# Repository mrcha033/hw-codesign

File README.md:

# hw-codesign

**Give an AI agent a hardware brief. Get KiCad, firmware, a 3D assembly, and an explicit fabrication-blocker report.**

Agentic hardware co-design from brief to KiCad, firmware, 3D review, and explicit
fabrication blockers. For 13 supported board families, `hw-codesign` turns a
prompt into a reviewable candidate while keeping missing sourcing, toolchain,
manufacturing, and physical evidence visible instead of silently treating it as
success.

<p align="center">
  
</p>

<p align="center">
  <strong><a href="https://mrcha033.github.io/hw-codesign/#assembly-title">Explore the interactive 3D review</a></strong><br>
  Rotate and zoom the generated RP2040 USB candidate, then inspect its evidence and unresolved blockers.
</p>

[Explore the interactive 3D review](https://mrcha033.github.io/hw-codesign/#assembly-title) ·
[Install from PyPI](https://pypi.org/project/hw-codesign/) ·
[Watch the 20-second demo](docs/demo/README.md) ·
[Read the validation contract](docs/validation-contract.md)

The render is a candidate-level CAD preview, not a photo of fabricated or
qualified hardware.

## Quickstart

Python 3.11 or newer is required. This public install path was smoke-tested in a
clean Python 3.11 environment against version 0.1.4.

```bash
python3.11 -m pip install "hw-codesign[mcp]==0.1.4"
mkdir my-hardware-workspace && cd my-hardware-workspace
hw --root . create-project my_usb_board --template rp2040_usb_device
hw --root . validate-spec my_usb_board
```

That creates and validates a typed RP2040 project. Continue to
[generate the full demo candidate](#generate-the-demo-candidate), or run
`hw --help` to inspect the CLI.

<details>
<summary><strong>What the public demo proves—and what remains blocked</strong></summary>

<!-- golden-demo-evidence:start -->
The demo is a dated full-toolchain repository run against the RP2040 USB-device
family. It produced a candidate, not a fabrication-qualified board: 44 of 48
recorded gates passed, 1 failed, and 3 were blocked. Freerouting reports zero
raw unrouted connections and KiCad reports zero post-fill unconnected items;
native ERC and DRC each report zero violations. The native Zephyr build is
blocked because the selected ARM toolchain lacks newlib runtime files.

The remaining evidence is material: sourcing fails, current supplier
availability is blocked, the native Zephyr build is blocked on ARM newlib, and
physical qualification is blocked. The
board has not been fabricated, and the U2.57 via-in-pad fill/cap/tent process is
unqualified. Bundle `7d6731501a24716965593f7fcdc168a3d739d1b0a1b7a57f7a0b29fee51c1b84` records those boundaries.
<!-- golden-demo-evidence:end -->

</details>

## The 20-second product loop

| Brief | Candidate | Blocker report |
|---|---|---|
| Natural-language constraints are lowered into typed project fields with provenance. | The run emits electronics source, KiCad artifacts, firmware, BOM, review bundle, and hashes. | Every gate is `pass`, `fail`, or `blocked`; physical evidence gaps stay release-blocking. |

`hw-codesign` is available as a CLI (`hw`), an MCP server (`hw-mcp`), and a
repository-owned agent plugin. Its design surface is template- and
contract-driven. It is not an arbitrary-prompt PCB oracle.

## Install

Python 3.11 or newer is required.

```bash
python3.11 -m pip install "hw-codesign[mcp]==0.1.4"
hw --help
```

The [v0.1.4 release](https://github.com/mrcha033/hw-codesign/releases/tag/v0.1.4)
also publishes a wheel, source distribution, standalone archives for Linux,
macOS, and Windows, a self-contained review, and checksums. The public container
is `ghcr.io/mrcha033/hw-codesign:0.1.4`.

### Development install

```bash
git clone https://github.com/mrcha033/hw-codesign.git
cd hw-codesign
python3.11 -m venv .venv
.venv/bin/pip install '.[mcp]'
export PATH="$PWD/.venv/bin:$PATH"
hw --help
```

The self-contained review is live at
https://mrcha033.github.io/hw-codesign/ and can be inspected without a receiver
or cloud account.

## Generate the demo candidate

Create the same candidate class used in the demo:

```bash
mkdir my-hardware-workspace
cd my-hardware-workspace

hw --root . create-project my_usb_board --template rp2040_usb_device
hw --root . update-requirements my_usb_board \
  "Design a 2-layer RP2040 USB HID and CDC board powered from USB-C. Use Zephyr."
hw --root . design-candidate my_usb_board --brief \
  "Design a 2-layer RP2040 USB HID and CDC board powered from USB-C. Use Zephyr."
hw --root . export-standalone-review my_usb_board
```

The generated HTML review is self-contained. No receiver or cloud account is
required to inspect it.

### MCP clients

Claude Desktop configuration:

```json
{
  "mcpServers": {
    "hw-codesign": {
      "command": "/absolute/path/to/hw-codesign/.venv/bin/hw-mcp",
      "args": [],
      "env": {
        "HW_PLATFORM_ROOT": "/absolute/path/to/a/writable/hardware-workspace"
      }
    }
  }
}
```

Claude Code:

```bash
claude mcp add hw-codesign \
  -e HW_PLATFORM_ROOT="$PWD" \
  -- /absolute/path/to/hw-codesign/.venv/bin/hw-mcp
```

For Codex or Claude plugin use, clone this repository and install the
`hw-codesign` marketplace entry:

```bash
codex plugin marketplace add /absolute/path/to/hw-codesign
codex plugin add hw-codesign@hw-codesign
```

## What the statuses mean

| Status | Meaning |
|---|---|
| `pass` | The named gate ran and its declared checks passed. |
| `fail` | The gate ran and found a concrete defect or unmet contract. |
| `blocked` | Evidence or a required tool/input is missing. This is never treated as pass. |
| `candidate` | Reviewable generated artifacts exist, but release promotion is not authorized. |
| `released` | The configured release gate passed and the release bundle was exported. This does not imply physical qualification unless physical evidence is present and approved. |

Every public tool response carries `release_eligible`, `candidate_only`, and
`release_blocking_failures`. Only the release-gate and release-export paths can
set `release_eligible: true`.

## Supported board families

All 13 shipped templates conform to the current typed spec schema. Their design
and physical maturity are not identical; inspect each candidate's gate report.

| Group | Templates |
|---|---|
| USB devices | `rp2040_usb_device`, `usb_hid_controller`, `avr_32u4_hid`, `nrf52840_dongle` |
| Sensors and gateways | `ble_sensor_node`, `sensor_data_logger`, `lora_sensor_node`, `esp32_wifi_gateway`, `samd21_sensor_hub`, `stm32g0_power_monitor` |
| Robotics and power | `robotics_controller_full`, `mini_servo_robot`, `bldc_esc` |

Use `hw diagnose-environment` to inspect the installed native backends, or see
[Adapting the design system](docs/adapting-a-spec.md) before adding a materially
different topology.

## Agent workflow

The MCP names use the same lifecycle as the CLI:

```text
hw_get_capabilities
  → hw_create_project
  → hw_update_requirements
  → hw_design_candidate
  → hw_check_cross_domain_consistency
  → hw_generate_physical_qualification_plan
  → hw_record_physical_evidence
  → hw_check_release_gate
  → hw_export_release_bundle
```

Agents can also author circuit blocks, placement constraints, and firmware
modules, explore alternatives, compare candidates, and run adversarial grounding
benchmarks. See the [MCP tool reference](docs/mcp-tools.md) for the complete
contract.

## Build with us

- [Reproduce the PyPI quickstart on a clean platform](https://github.com/mrcha033/hw-codesign/issues/11) — the current newcomer task.
- [Share a generated candidate](https://github.com/mrcha033/hw-codesign/discussions/categories/show-and-tell) — include the prompt, template, environment, and blocker report.
- [Help close sourcing or physical-evidence gaps](https://github.com/mrcha033/hw-codesign/issues?q=is%3Aissue+is%3Aopen+label%3A%22help+wanted%22) — software-clean is not the end of the hardware lifecycle.

If a new board family or backend is your goal, start with
[Adapting the design system](docs/adapting-a-spec.md) and preserve the
`pass`/`fail`/`blocked` claim boundary in every new tool path.

## Repository map

| Path | Purpose |
|---|---|
| `src/hw_codesign/` | CLI, MCP service, generators, validators, and review UI |
| `src/hw_codesign/templates/` | Supported family specifications |
| `parts/` | Curated components, role sets, supplier records, and datasheet evidence |
| `projects/golden_rp2040_usb_hid/` | Date-stamped golden candidate and current evidence gaps |
| `docs/demo/` | 20-second demo and self-contained read-only review |
| `schemas/` | Typed project and result contracts |
| `tests/` | Cross-platform regression and evidence-boundary tests |

## Development

```bash
python3.11 -m venv .venv
.venv/bin/pip install '.[dev,mcp]'
npm ci --ignore-scripts
pytest -q
ruff check .
```

Native gates require their corresponding tools. Diagnose the current machine
before interpreting a blocked result:

```bash
hw diagnose-environment --target fabrication_release --backend kicad
hw check my_usb_board
```

See [CONTRIBUTING.md](CONTRIBUTING.md) for contribution scope, tests, and claim
boundaries. Security reports should follow [SECURITY.md](SECURITY.md).

## Known limits

- Generated artifacts remain candidates until every configured release gate
  passes. A Gerber ZIP is not proof that a board is safe or manufacturable.
- Digital checks cannot certify thermal performance, EMI/EMC, vibration,
  ingress, abuse safety, connector life, assembly quality, or electrical
  bring-up. Those require traceable physical evidence.
- The RP2040 golden candidate has not yet been fabricated. Its current blocker
  report is published deliberately, and no bench measurements are claimed.
- Supplier catalog entries identify parts and provenance, but current stock and
  alternates require fresh supplier evidence.
- The receiver binds only to loopback. Remote use requires an authenticated SSH
  tunnel or reverse proxy; it is not a multi-tenant hosted service.

## License

The project is licensed under [Apache-2.0](LICENSE). The vendored KiCad footprint
under `src/hw_codesign/footprints/` retains its CC-BY-SA 4.0 license with the
KiCad libraries exception; see [NOTICE](NOTICE) for the boundary.

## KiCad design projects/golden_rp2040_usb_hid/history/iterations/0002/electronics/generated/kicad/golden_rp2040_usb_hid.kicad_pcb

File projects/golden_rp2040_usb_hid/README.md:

# RP2040 USB HID golden candidate

This is the first deliberately simple `hw-codesign` golden-board candidate. It
is intended to become a physically brought-up reference board, but the current
snapshot is **not fabrication-qualified and has not been ordered**.

## Brief

> Design a 2-layer RP2040 USB HID and CDC board powered from USB-C, with 2 MB
> QSPI flash, a 12 MHz crystal, USB ESD protection, SWD debug, 1 ms HID reports,
> and enumeration within 500 ms. Use Zephyr and keep the board within 65 mm by
> 30 mm.

## Current evidence

- The current spec schema passes with zero errors.
- The resolved graph contains 31 manufacturer-identified components and 24
  named nets.
- A real KiCad schematic is generated with 36 intentional no-connect markers;
  native KiCad ERC passes with zero violations.
- The tscircuit layout places all 31 components with parity, emits 91 traces,
  and reports zero PCB validation errors.
- Freerouting records zero raw unrouted connections; the persisted zone fill has
  zero post-import unconnected items, and native KiCad DRC has zero violations.
- The native RP2040 Zephyr build is blocked because ARM newlib runtime files
  (`nosys.specs`, `libc.a`, `libnosys.a`) are unavailable; no firmware build
  completion is claimed.
- Electronics, mechanical, firmware, BOM, candidate fabrication, and review
  artifacts were generated.
- The dated full-toolchain review records 48 gates: 44 pass, 1 fail, 3 blocked.
- Review bundle hash:
  `7d6731501a24716965593f7fcdc168a3d739d1b0a1b7a57f7a0b29fee51c1b84`.

Open the repository demo and review in [`docs/demo`](../../docs/demo/README.md).

## Release blockers

- Current supplier availability and critical-role resilience need fresh,
  timestamped evidence; `sourcing` fails, while `sourcing_resilience` passes and
  `supplier_availability` remains blocked. The native Zephyr build is also
  blocked because ARM newlib runtime files are unavailable.
- U2 exposed pad U2.57 uses a via-in-pad connection. Native DRC acceptance does
  not qualify its tented, plugged, filled, or capped fabrication process; the
  required stack-up/fabricator capability and acceptance evidence are open.
- The candidate has not been fabricated or ordered. Assembly inspection,
  current-limited power-up, rail measurements, firmware interface bring-up,
  thermal, SI/PI, EMI, vibration/retention, and ESD/ingress evidence are absent.

The qualification checklist is in
[`validation/physical/qualification_plan.md`](validation/physical/qualification_plan.md).
Physical evidence must be captured with artifact hashes and approval status via
`hw record-physical-evidence`; prose in this README cannot close a gate.

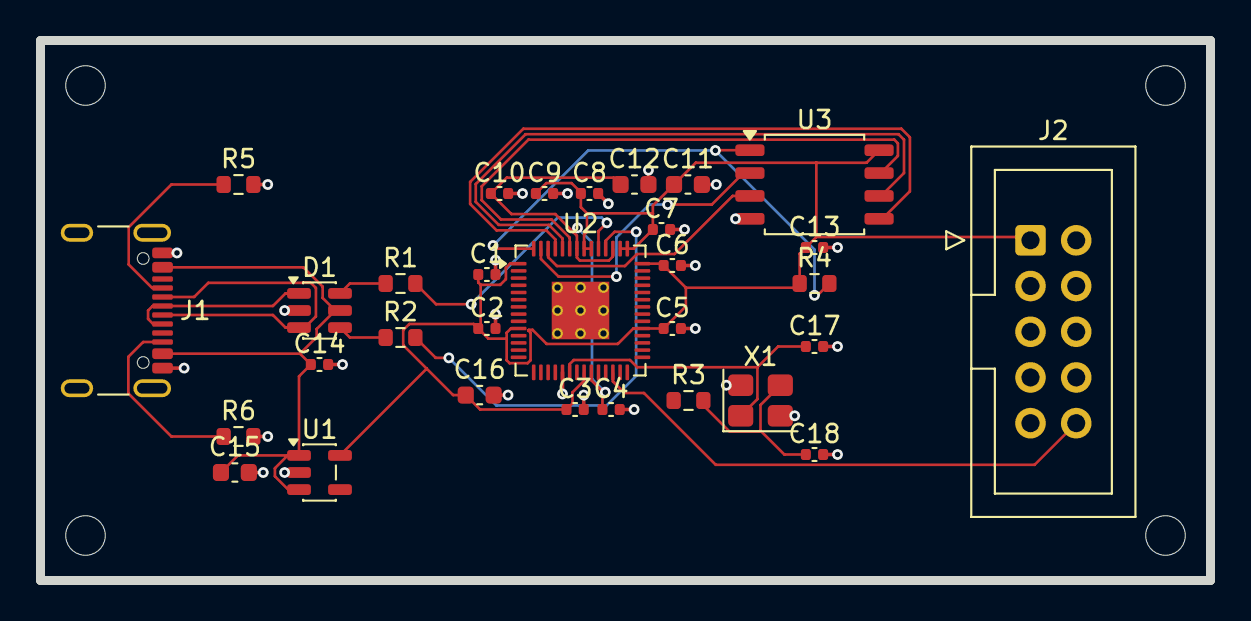
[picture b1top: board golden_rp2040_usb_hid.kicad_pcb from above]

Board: 2 copper layers, 65.0 x 30.0 mm, 35 parts (0 on the bottom side), 24 nets.

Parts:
C1, C2, C3, C4, C5, C6, C7, C8, C9, C10: 100nF; C_0402_1005Metric
C11: 1uF VREG_VIN; C_0603_1608Metric
C12: 1uF VREG_VOUT; C_0603_1608Metric
C13: 100nF FLASH; C_0402_1005Metric
C14: 100nF USB ESD VBUS; C_0402_1005Metric
C15: 1uF LDO input; C_0603_1608Metric
C16: 1uF LDO output; C_0603_1608Metric
C17, C18: 15pF XTAL; C_0402_1005Metric
D1: USB 2.0 ESD; SOT-23-6
H1, H2, H3, H4: MountingHole; MountingHole_2.2mm_Pad
J1: USB-C 2.0; USB_C_Receptacle_GCT_USB4105-xx-A_16P_TopMnt_Horizontal
J2: Cortex 10-pin SWD; IDC-Header_2x05_P2.54mm_Vertical
R1: 27R USB D+; R_0603_1608Metric
R2: 27R USB D-; R_0603_1608Metric
R3: 1K XTAL damping; R_0603_1608Metric
R4: 10K QSPI CS pull-up; R_0603_1608Metric
R5, R6: 5K1 USB-C Rd; R_0603_1608Metric
U1: 3V3 LDO; SOT-23-5
U2: RP2040; QFN-56-1EP_7x7mm_P0.4mm_EP3.2x3.2mm
U3: 16Mbit QSPI Flash; SOIC-8_5.3x5.3mm_P1.27mm
X1: 12MHz RP2040 crystal; Crystal_SMD_3225-4Pin_3.2x2.5mm

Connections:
GND: C1.2, C2.2, C3.2, C4.2, C5.2, C6.2, C7.2, C8.2, C9.2, C10.2, C11.2, C12.2, C13.2, C14.2, C15.2, C16.2, C17.2, C18.2, D1.2, J1.A1, J1.A12, J1.B1, J1.B12, J1.SH, J2.3, J2.5, J2.9, R5.2, R6.2, U1.2, U2.19, U2.57, U3.4, X1.2, X1.4
MCU_RUN: J2.10, U2.26
QSPI_CLK: U2.52, U3.6
QSPI_CS: R4.2, U2.56, U3.1
QSPI_D2: U2.54, U3.3
QSPI_D3: U2.51, U3.7
QSPI_MISO: U2.55, U3.2
QSPI_MOSI: U2.53, U3.5
SWCLK: J2.4, U2.24
SWDIO: J2.2, U2.25
USB_CC1: J1.A5, R5.1
USB_CC2: J1.B5, R6.1
USB_DM: R2.2, U2.46
USB_DM_ESD: D1.4, R2.1
USB_DM_RAW: D1.3, J1.A7, J1.B7
USB_DP: R1.2, U2.47
USB_DP_ESD: D1.6, R1.1
USB_DP_RAW: D1.1, J1.A6, J1.B6
USB_VBUS: C14.1, C15.1, D1.5, J1.A4, J1.A9, J1.B4, J1.B9, U1.1, U1.3
V1V1: C4.1, C10.1, C12.1, U2.23, U2.45, U2.50
V3V3: C1.1, C2.1, C3.1, C5.1, C6.1, C7.1, C8.1, C9.1, C11.1, C13.1, C16.1, J2.1, R4.1, U1.5, U2.1, U2.10, U2.22, U2.33, U2.42, U2.43, U2.44, U2.48, U2.49, U3.8
XIN: C17.1, U2.20, X1.1
XOUT: R3.1, U2.21
XTAL_RETURN: C18.1, R3.2, X1.3

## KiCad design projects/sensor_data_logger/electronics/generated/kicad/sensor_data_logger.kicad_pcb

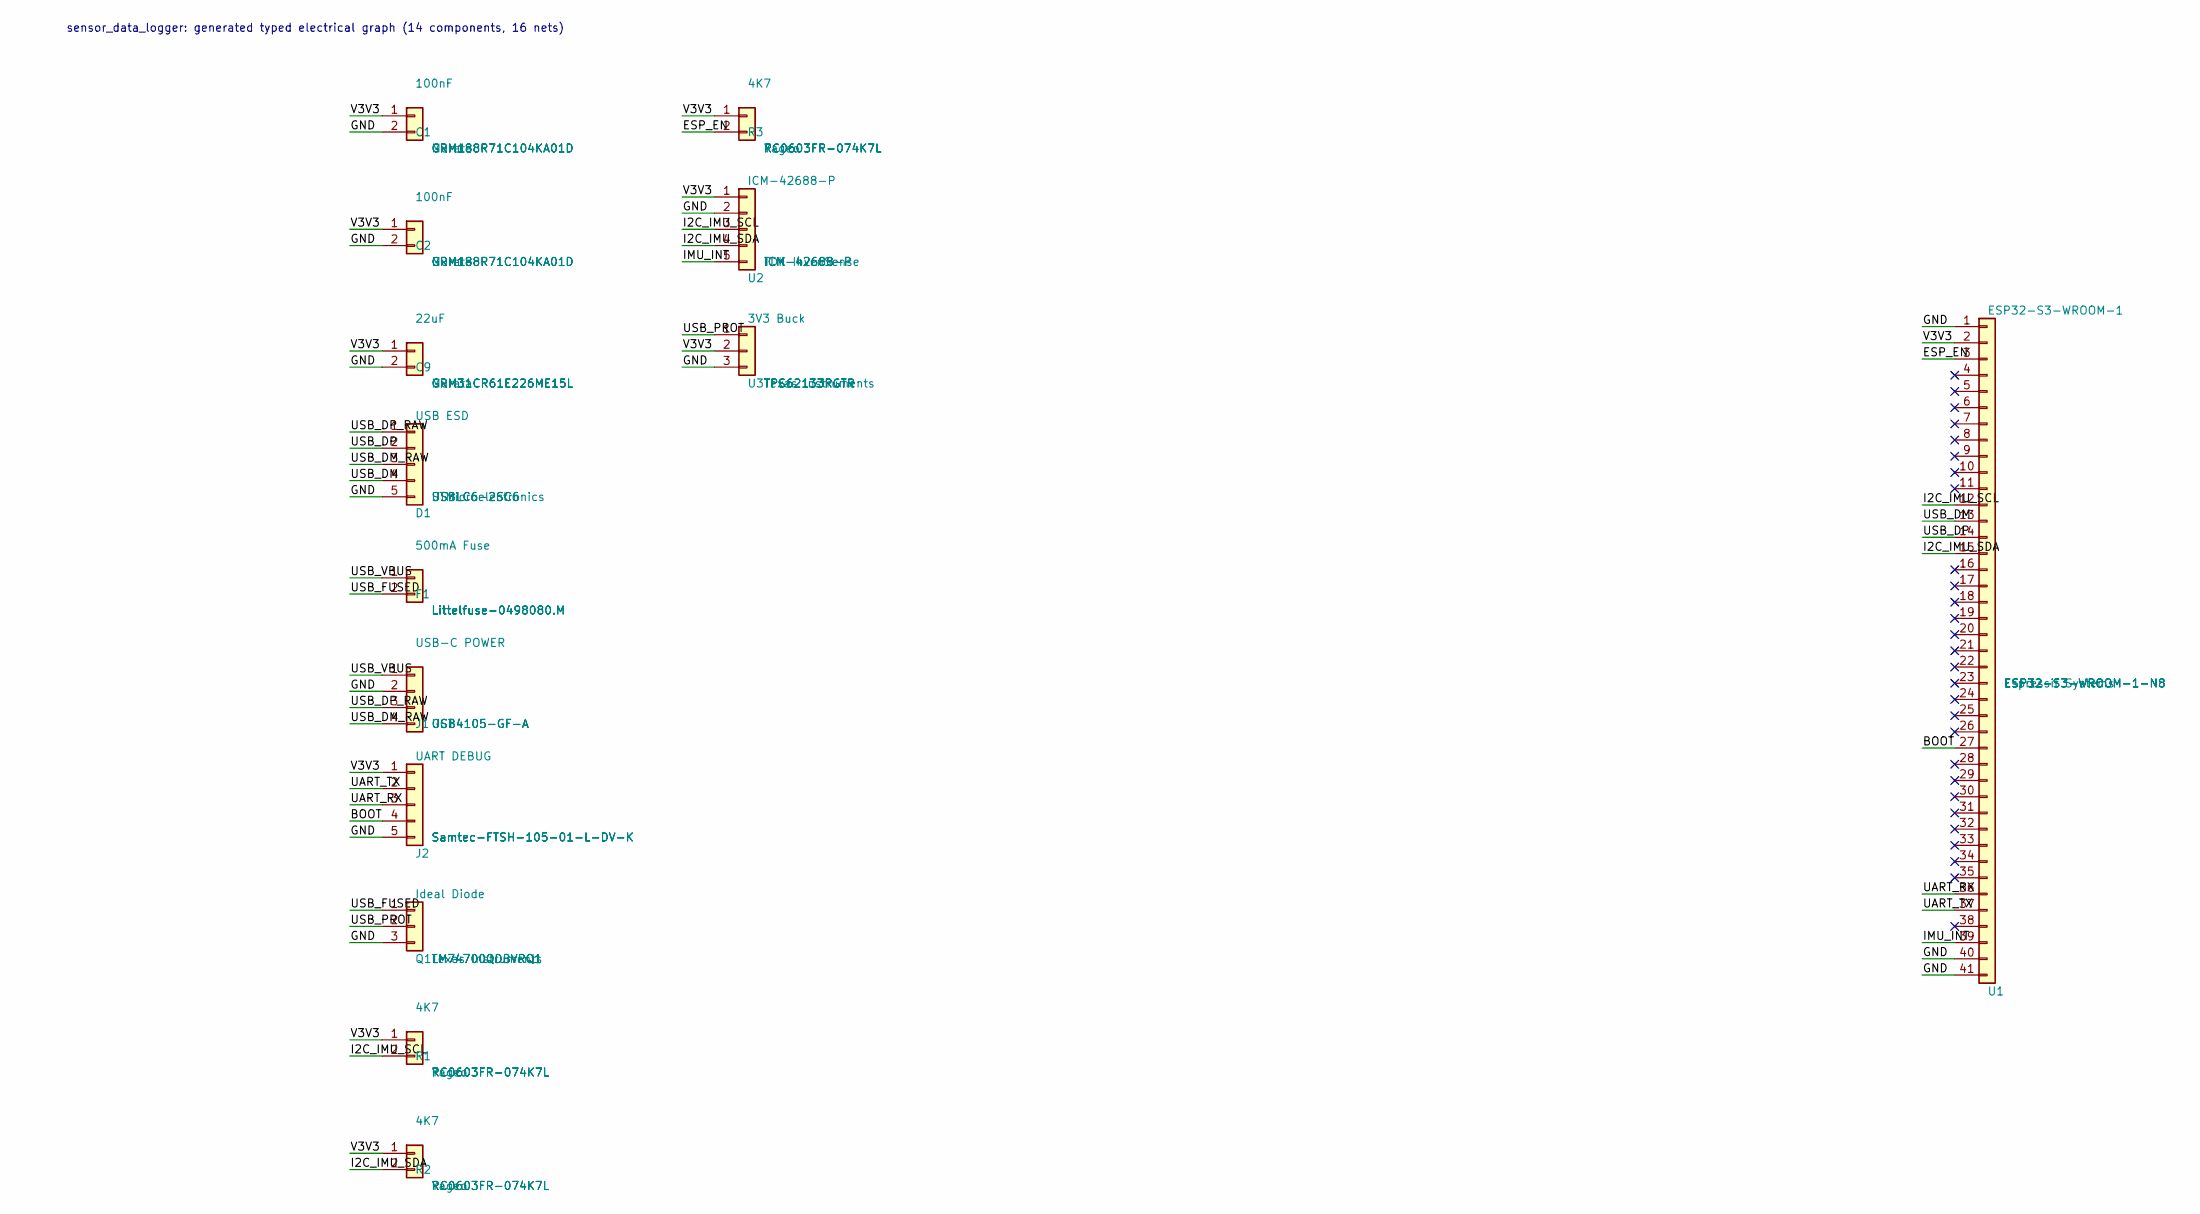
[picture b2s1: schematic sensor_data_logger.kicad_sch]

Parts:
C1, C2: 100nF; C0603; MPN GRM188R71C104KA01D
C9: 22uF; C1206; MPN GRM31CR61E226ME15L
D1: USB ESD; SOT23-6; MPN USBLC6-2SC6
F1: 500mA Fuse; MIDI; MPN Littelfuse-0498080.M
J1: USB-C POWER; USB_C_16Pin; MPN USB4105-GF-A
J2: UART DEBUG; Cortex_Debug_10Pin; MPN Samtec-FTSH-105-01-L-DV-K
Q1: Ideal Diode; SOT23-6; MPN LM74700QDBVRQ1
R1, R2, R3: 4K7; R0603; MPN RC0603FR-074K7L
U1: ESP32-S3-WROOM-1; MPN ESP32-S3-WROOM-1-N8
U2: ICM-42688-P; LGA14; MPN ICM-42688-P
U3: 3V3 Buck; VQFN16; MPN TPS62133RGTR

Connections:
BOOT: J2.4, U1.27
ESP_EN: R3.2, U1.3
GND: C1.2, C2.2, C9.2, D1.5, J1.2, J2.5, Q1.3, U1.1, U1.40, U1.41, U2.2, U3.3; also elsewhere on the board
I2C_IMU_SCL: R1.2, U1.12, U2.3
I2C_IMU_SDA: R2.2, U1.15, U2.4
IMU_INT: U1.39, U2.5
UART_RX: J2.3, U1.36
UART_TX: J2.2, U1.37
USB_CC1: J1.5; also elsewhere on the board
USB_CC2: J1.6; also elsewhere on the board
USB_DM: D1.4, U1.13
USB_DM_RAW: D1.3, J1.4
USB_DP: D1.2, U1.14
USB_DP_RAW: D1.1, J1.3
USB_FUSED: F1.2, Q1.1
USB_PROT: Q1.2, U3.1
USB_VBUS: F1.1, J1.1
V3V3: C1.1, C2.1, C9.1, J2.1, R1.1, R2.1, R3.1, U1.2, U2.1, U3.2

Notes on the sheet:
sensor_data_logger: generated typed electrical graph (14 components, 16 nets)

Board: 2 copper layers, 20 parts (0 on the bottom side), 18 nets, no tracks yet.

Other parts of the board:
H1, H2, H3, H4: MountingHole; MountingHole_3.2mm_Pad
R5, R6: 5K1 USB-C Rd; R_0603_1608Metric

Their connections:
GND: R5.2, R6.2; also elsewhere on the board
USB_CC1: R5.1; also elsewhere on the board
USB_CC2: R6.1; also elsewhere on the board

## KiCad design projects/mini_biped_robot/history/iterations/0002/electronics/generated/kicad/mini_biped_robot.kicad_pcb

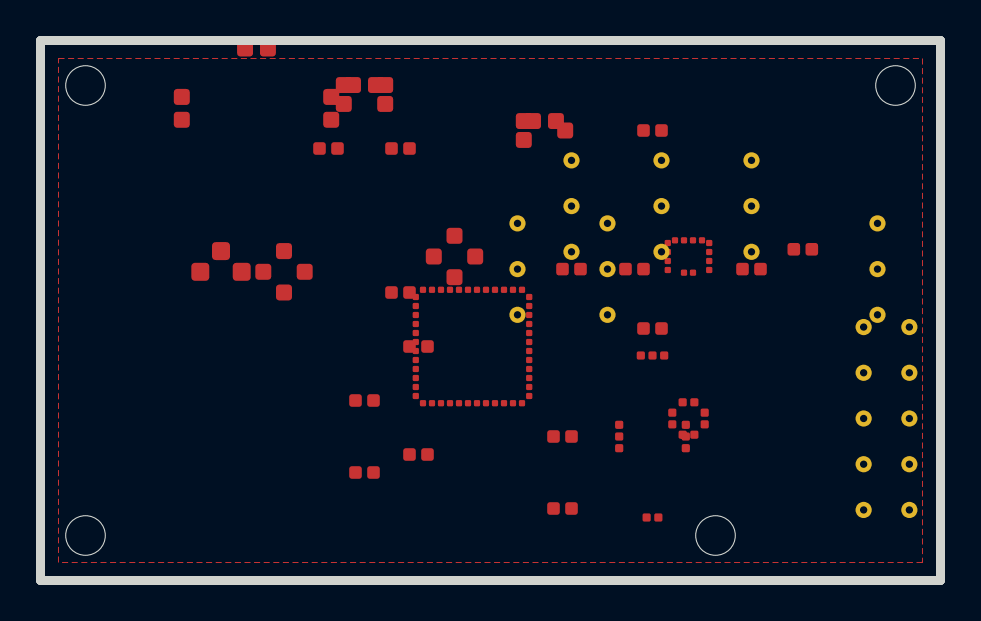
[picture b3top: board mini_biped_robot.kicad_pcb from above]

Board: 2 copper layers, 50.0 x 30.0 mm, 36 parts (0 on the bottom side), 29 nets, no tracks yet.

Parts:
C1, C2: 100nF; C_0402_1005Metric
C3: 10uF; C_0603_1608Metric
C4, C5: 12pF RTC XTAL; C_0805_2012Metric
C6: 1uF VDDCORE; C_0603_1608Metric
C20: 1000uF 10V LOW ESR; C_0603_1608Metric
D1: USB ESD; SOT-23-6
F20: 10A SERVO FUSE; Fuseholder_Blade_Mini
H1, H2, H3, H4: MountingHole; MountingHole_2.2mm_Pad
J1: USB-C POWER; USB_C_GCT_USB4105
J2: SWD 10-pin; PinHeader_2x05_P2.54mm_Vertical
J20: 2S LIPO INPUT; XT30PW_M
J21: SERVO_1_3PIN; PinHeader_1x03_P2.54mm_Vertical
J22: SERVO_2_3PIN; PinHeader_1x03_P2.54mm_Vertical
J23: SERVO_3_3PIN; PinHeader_1x03_P2.54mm_Vertical
J24: SERVO_4_3PIN; PinHeader_1x03_P2.54mm_Vertical
J25: SERVO_5_3PIN; PinHeader_1x03_P2.54mm_Vertical
J26: SERVO_6_3PIN; PinHeader_1x03_P2.54mm_Vertical
J27: NC E-STOP LOOP; TerminalBlock_1x03_P5.08mm
R1: 4K7 SCL PU; R_0603_1608Metric
R2: 4K7 SDA PU; R_0603_1608Metric
R3, R4: 5K1 USB-C Rd; R_0603_1608Metric
R20: 10K E-STOP FAIL-SAFE PULLDOWN; R0603
U1: 3V3 LDO; SOT-23-5
U2: SAMD21G18A; TQFP-48_7x7mm_P0.5mm
U3: LSM6DSOX; LGA-14_3x2.5mm_P0.5mm
U4: BME280; Bosch_LGA-8_2.5x2.5mm_P0.65mm
U20: 5V 9A STEP-DOWN MODULE; MODULE_POLOLU_D24V90F5
U21: 16-CHANNEL I2C PWM; TSSOP-28_4.4x9.7mm_P0.65mm
U22: E-STOP PWM INVERTER; SOT-23-5
X1: 32.768kHz XTAL; Crystal_SMD_Epson_MC-306_3.2x1.5mm

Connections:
ESTOP_OK: J27.2, R20.1, U20.4, U22.3
GND: C1.2, C2.2, C3.2, C4.2, C5.2, C6.2, C20.2, D1.5, J1.2, J2.3, J2.5, J2.9, J20.2, J21.3, J22.3, J23.3, J24.3, J25.3, J26.3, J27.3, R3.2, R4.2, R20.2, U1.2, U2.10, U2.18, U2.36, U3.1, U3.7, U3.8, U4.3, U4.6, U4.8, U20.2, U21.2, U22.2
I2C_SCL: R1.2, U2.32, U3.3, U4.5, U21.3
I2C_SDA: R2.2, U2.31, U3.2, U4.4, U21.4
IMU_INT1: U2.27, U3.4
MCU_NRST: J2.10, U2.40
SERVO1_PWM: J21.1, U21.6
SERVO2_PWM: J22.1, U21.7
SERVO3_PWM: J23.1, U21.8
SERVO4_PWM: J24.1, U21.9
SERVO5_PWM: J25.1, U21.10
SERVO6_PWM: J26.1, U21.11
SERVO_PWM_OE: U21.5, U22.4
SWCLK: J2.4, U2.46
SWDIO: J2.2, U2.47
USB_CC1: J1.5, R3.1
USB_CC2: J1.6, R4.1
USB_DM: D1.4, U2.33
USB_DM_RAW: D1.3, J1.4
USB_DP: D1.2, U2.34
USB_DP_RAW: D1.1, J1.3
USB_VBUS: J1.1, U1.1, U1.3
V3V3: C1.1, C2.1, C3.1, J2.1, J27.1, R1.1, R2.1, U1.5, U2.9, U2.17, U2.35, U2.43, U3.6, U3.9, U3.14, U4.1, U4.2, U4.7, U21.1, U22.1
V5: C20.1, J21.2, J22.2, J23.2, J24.2, J25.2, J26.2, U20.3
VBAT_FUSED: F20.2, U20.1
VBAT_RAW: F20.1, J20.1
VDDCORE: C6.1, U2.42
XIN32: C4.1, U2.1, X1.1
XOUT32: C5.1, U2.2, X1.2

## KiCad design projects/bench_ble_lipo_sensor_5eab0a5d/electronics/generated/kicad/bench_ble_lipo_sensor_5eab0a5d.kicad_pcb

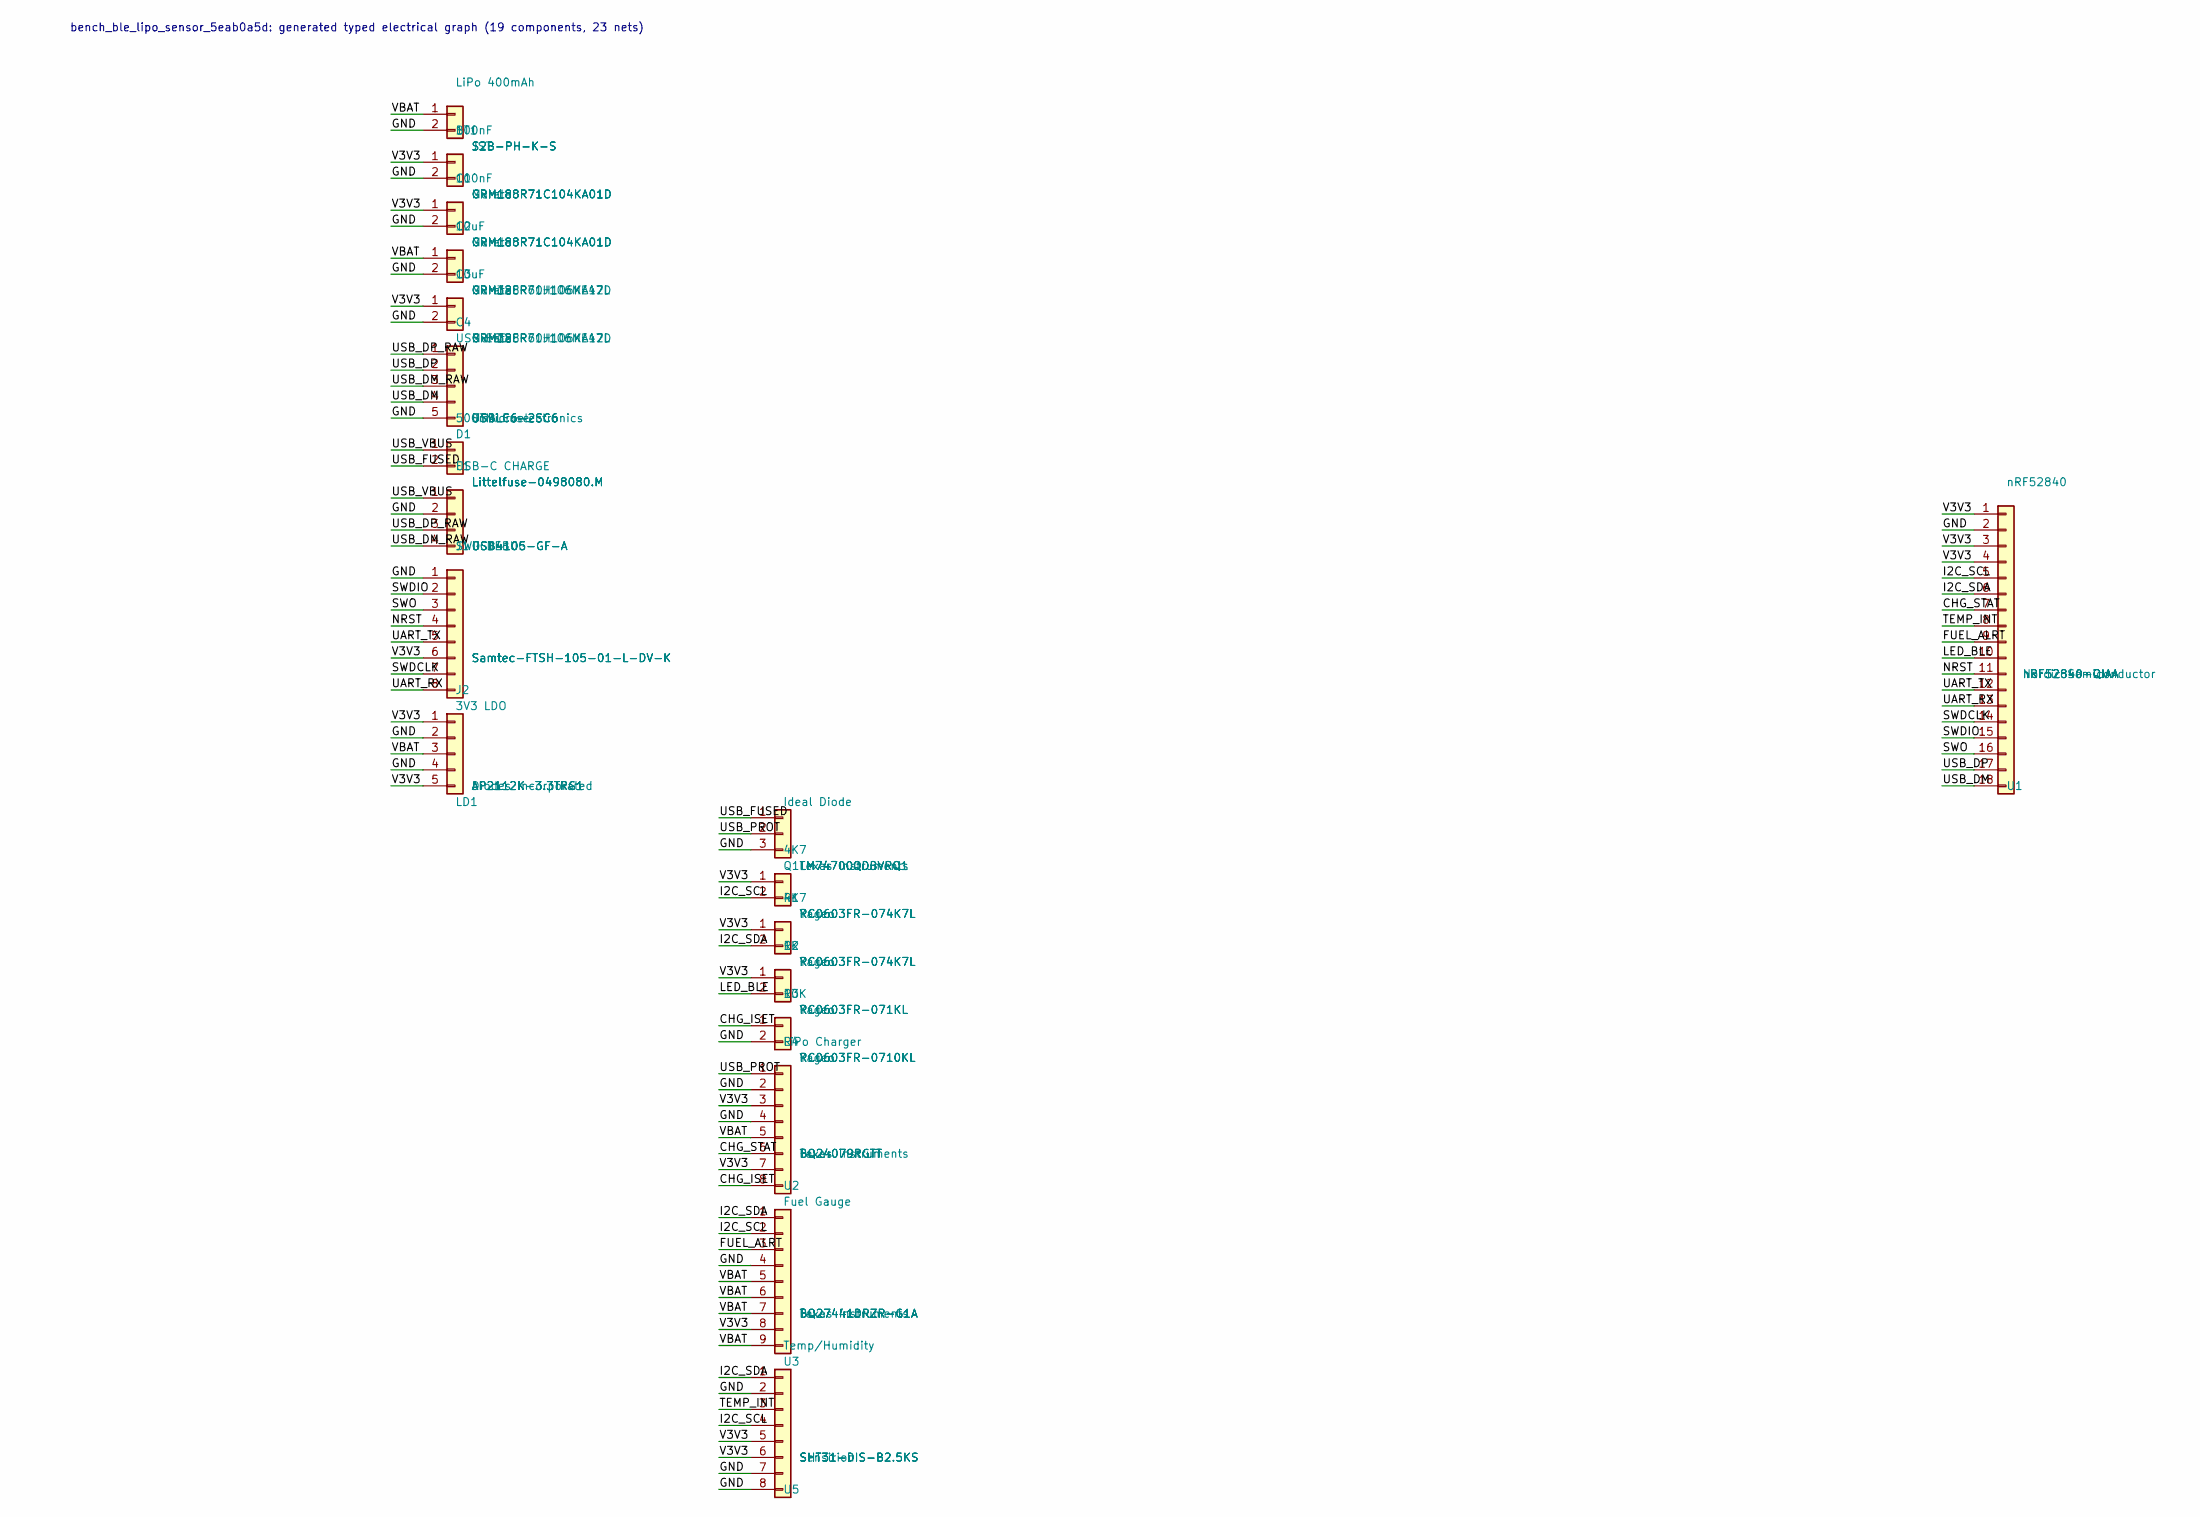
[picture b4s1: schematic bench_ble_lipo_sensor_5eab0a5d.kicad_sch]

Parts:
BT1: LiPo 400mAh; JST_PH_S2B-PH-K_1x02_P2.00mm_Horizontal; MPN S2B-PH-K-S
C1, C2: 100nF; C_0603_1608Metric; MPN GRM188R71C104KA01D
C3, C4: 10uF; C_1210_3225Metric; MPN GRM32ER71H106KA12L
D1: USB ESD; SOT-23-6; MPN USBLC6-2SC6
F1: 500mA Fuse; MIDI_Fuse; MPN Littelfuse-0498080.M
J1: USB-C CHARGE; USB_C_GCT_USB4105; MPN USB4105-GF-A
J2: SWD DEBUG; FTSH-105; MPN Samtec-FTSH-105-01-L-DV-K
LD1: 3V3 LDO; SOT-23-5; MPN AP2112K-3.3TRG1
Q1: Ideal Diode; SOT-23-6; MPN LM74700QDBVRQ1
R1, R2: 4K7; R_0603_1608Metric; MPN RC0603FR-074K7L
R3: 1K; R_0603_1608Metric; MPN RC0603FR-071KL
R4: 10K; R_0603_1608Metric; MPN RC0603FR-0710KL
U1: nRF52840; nRF52840-QIAA; MPN nRF52840-QIAA
U2: LiPo Charger; SOT-23-8; MPN BQ24079RGTT
U3: Fuel Gauge; VSON-9_2x3mm_P0.5mm; MPN BQ27441DRZR-G1A
U5: Temp/Humidity; DFN-8-1EP_2x2.5mm_P0.5mm; MPN SHT31-DIS-B2.5KS

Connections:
CHG_ISET: R4.1, U2.8
CHG_STAT: U1.7, U2.6
FUEL_ALRT: U1.9, U3.3
GND: BT1.2, C1.2, C2.2, C3.2, C4.2, D1.5, J1.2, J2.1, LD1.2, LD1.4, Q1.3, R4.2, U1.2, U2.2, U2.4, U3.4, U5.2, U5.7, U5.8
I2C_SCL: R1.2, U1.5, U3.2, U5.4
I2C_SDA: R2.2, U1.6, U3.1, U5.1
LED_BLE: R3.2, U1.10
NRST: J2.4, U1.11
SWDCLK: J2.7, U1.14
SWDIO: J2.2, U1.15
SWO: J2.3, U1.16
TEMP_INT: U1.8, U5.3
UART_RX: J2.8, U1.13
UART_TX: J2.5, U1.12
USB_DM: D1.4, U1.18
USB_DM_RAW: D1.3, J1.4
USB_DP: D1.2, U1.17
USB_DP_RAW: D1.1, J1.3
USB_FUSED: F1.2, Q1.1
USB_PROT: Q1.2, U2.1
USB_VBUS: F1.1, J1.1
V3V3: C1.1, C2.1, C4.1, J2.6, LD1.1, LD1.5, R1.1, R2.1, R3.1, U1.1, U1.3, U1.4, U2.3, U2.7, U3.8, U5.5, U5.6
VBAT: BT1.1, C3.1, LD1.3, U2.5, U3.5, U3.6, U3.7, U3.9

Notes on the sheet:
bench_ble_lipo_sensor_5eab0a5d: generated typed electrical graph (19 components, 23 nets)

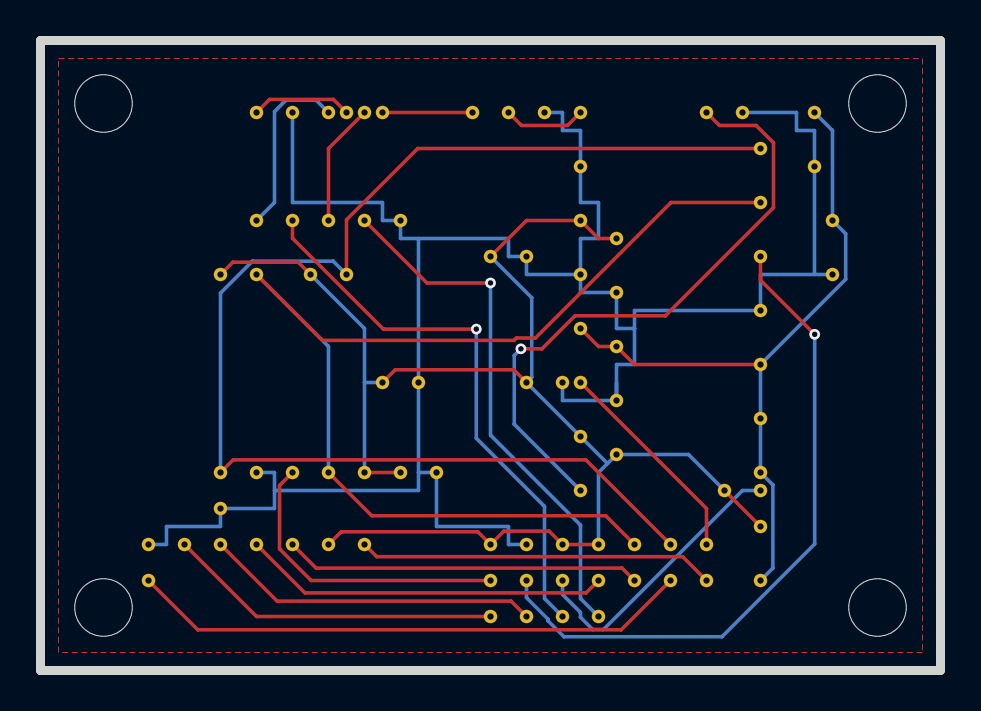
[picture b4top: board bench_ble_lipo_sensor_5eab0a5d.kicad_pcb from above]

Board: 2 copper layers, 50.0 x 35.0 mm, 23 parts (0 on the bottom side), 23 nets.

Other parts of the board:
H1, H2, H3, H4: MountingHole; MountingHole_3.2mm_Pad

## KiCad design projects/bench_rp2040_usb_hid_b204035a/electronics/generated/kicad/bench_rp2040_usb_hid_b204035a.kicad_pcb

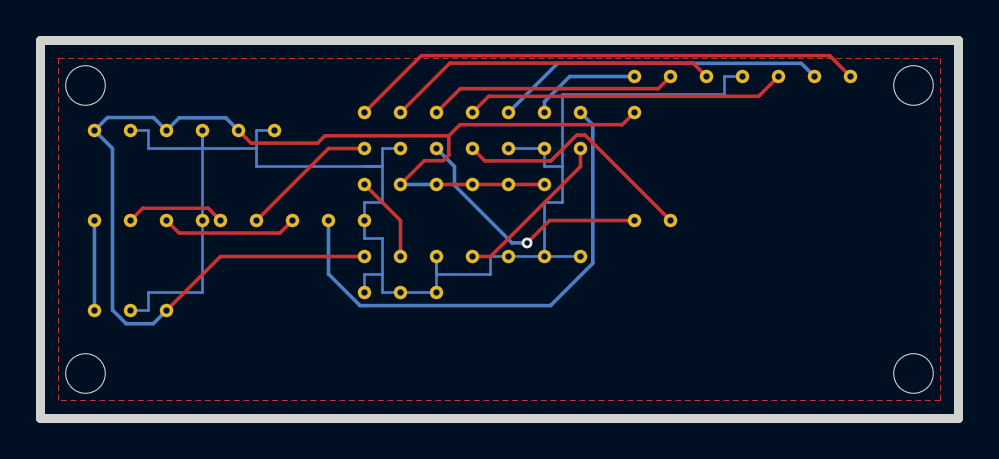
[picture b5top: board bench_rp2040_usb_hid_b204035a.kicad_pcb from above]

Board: 2 copper layers, 51.0 x 21.0 mm, 14 parts (0 on the bottom side), 17 nets.

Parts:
C1, C2: 100nF; C_0402_1005Metric
C3: 10uF; C_0603_1608Metric
D1: USB ESD; SOT-23-6
H1, H2, H3, H4: MountingHole; MountingHole_2.2mm_Pad
J1: USB-C POWER; USB_C_GCT_USB4105
J2: SWD 10-pin; PinHeader_2x05_P2.54mm_Vertical
U1: 3V3 LDO; SOT-23-5
U2: RP2040; QFN-56-1EP_7x7mm_P0.4mm_EP3.2x3.2mm
U3: 2MB QSPI; SOIC-8_3.9x4.9mm_P1.27mm
X1: 12MHz XTAL; Crystal_SMD_HC-49S

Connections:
GND: C1.2, C2.2, C3.2, D1.5, J1.4, J2.3, J2.5, J2.6, J2.7, J2.8, J2.9, J2.10, U1.2, U2.16, U2.33, U2.34, U3.4
QSPI_CLK: U2.5, U3.6
QSPI_CS: U2.6, U3.1
QSPI_D2: U2.2, U3.3
QSPI_D3: U2.1, U3.7
QSPI_MISO: U2.3, U3.2
QSPI_MOSI: U2.4, U3.5
SWCLK: J2.4, U2.40
SWDIO: J2.2, U2.41
USB_DM: D1.4, U2.11
USB_DM_RAW: D1.3, J1.3
USB_DP: D1.2, U2.12
USB_DP_RAW: D1.1, J1.2
USB_VBUS: J1.1, U1.1
V3V3: C1.1, C2.1, C3.1, J2.1, U1.3, U2.44, U2.45, U2.46, U2.47, U2.48, U3.8
XIN: U2.17, X1.1
XOUT: U2.18, X1.2
